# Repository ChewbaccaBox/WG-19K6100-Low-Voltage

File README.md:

# WG-19K6100-Low-Voltage
My version of the low voltage replacement board for the 6100 monitor.\
Larger / Through-hole parts provide beter thermals.\
Adjustable voltage range = +/- 23.5v - 28.5v \
&nbsp;

**BILL OF MATERIALS** :\
Includes example digikey item #'s

**1 * LM317 ( TO-220 pkg.)**\
&nbsp;&nbsp;&nbsp;&nbsp; DGK: LM317TG \
**1 * LM337 ( TO-220 pkg.)**\
&nbsp;&nbsp;&nbsp;&nbsp; DGK: LM3137TG \
**2 * 1k Trimmer Pot (PCB can fit both '.' and ... pin types, 0.1" spacing)**\
&nbsp;&nbsp;&nbsp;&nbsp; DGK: 500E-0331 or DGK:3306W-1-102\
**6 * 1N4007 Diode**\
**4 * 2.2uF 50V Capacitor**\
**2 * 10uF 50V Capacitor**\
**2 * 240 Ohm Resistor 1/4W**\
**4 * 4.5k Ohm Resistor 1/4W**\
**5 * WIRES TO RAISE PCB OVER BOARD**

**(OPTIONAL) 2 * TO-220 Compact Heatsink + Insulator/Thermal Pad** \
&nbsp;&nbsp;&nbsp;&nbsp; DGK: 577102B00000G + SP400-0.007-00-54 \
&nbsp;

**TESTING STATUS:**

Multiple installed and working in revisions P314 and P327.\
The filter capicators of the deflection board are closer to the connector on revision P327, so it is a little tighter, but will still work.

**INSTALLATION INSTRUCTIONS:**

To be written... Stay tuned!

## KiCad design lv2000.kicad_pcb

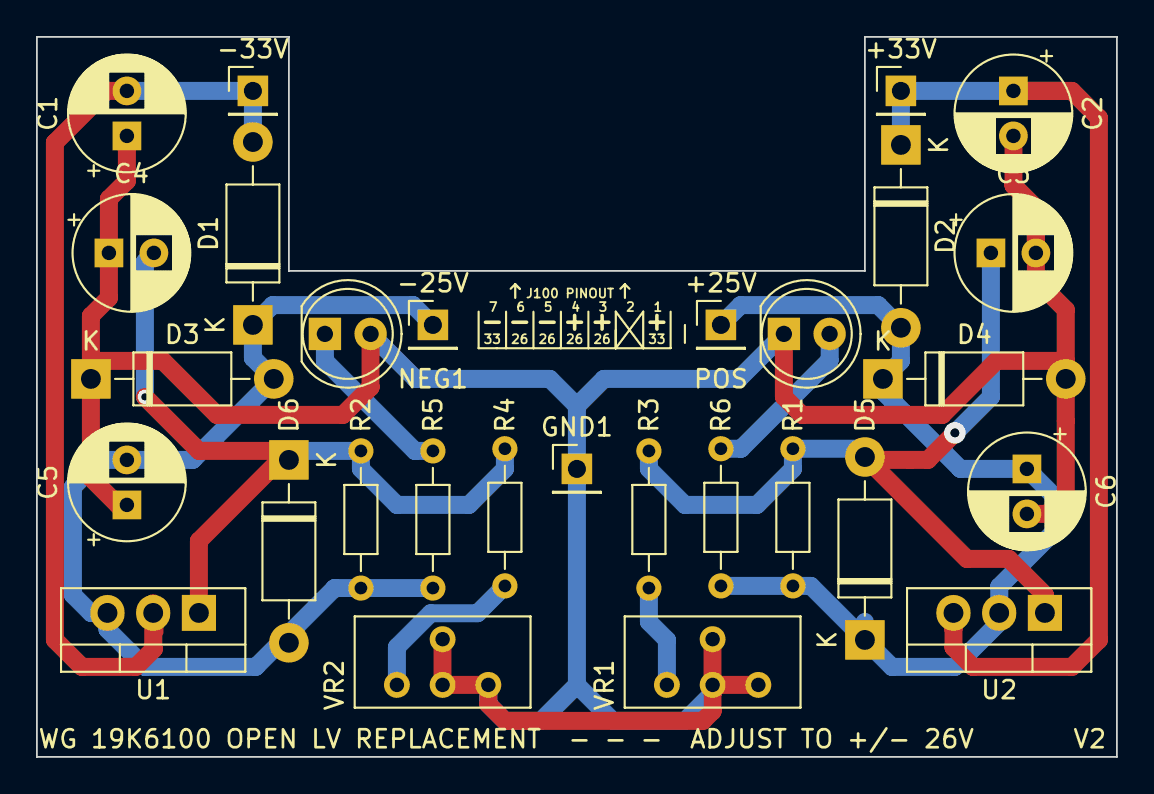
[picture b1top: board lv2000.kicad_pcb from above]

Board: 2 copper layers, 60.0 x 40.0 mm, 29 parts (0 on the bottom side), 11 nets.

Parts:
+25V, +33V: Conn_01x01_Male; PinHeader_1x01_P2.54mm_Vertical
-25V, -33V: Conn_01x01_Male; PinHeader_1x01_P2.54mm_Vertical
C1, C2, C3, C4, C5, C6: CP; CP_Radial_D6.3mm_P2.50mm
D1, D2, D3, D4, D5, D6: D; D_DO-41_SOD81_P10.16mm_Horizontal
GND1: Conn_01x01_Male; PinHeader_1x01_P2.54mm_Vertical
NEG1: LED; LED_D5.0mm_Clear
POS: LED; LED_D5.0mm_Clear
R1, R2, R3, R4, R5, R6: R; R_Axial_DIN0204_L3.6mm_D1.6mm_P7.62mm_Horizontal
U1: LM337_TO220; TO-220-3_Vertical
U2: LM317_TO-220; TO-220-3_Vertical
VR1, VR2: R_POT; Potentiometer_Bourns_3386C_Horizontal

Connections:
GND: C1.1, C2.2, C3.2, C4.1, C5.1, C6.2, D3.1, D4.2, GND1.1, NEG1.2, POS.1, VR1.2, VR1.3, VR2.2, VR2.3
unnamed: +25V.1, C6.1, D2.2, D4.1, D5.1, R1.1, R6.1, U2.2
unnamed: +33V.1, C2.1, D2.1, U2.3
unnamed: -25V.1, C5.2, D1.1, D3.2, D6.2, R2.2, R5.2, U1.3
unnamed: -33V.1, C1.2, D1.2, U1.2
unnamed: C3.1, D5.2, R1.2, R3.1, U2.1
unnamed: C4.2, D6.1, R2.1, R4.2, U1.1
unnamed: NEG1.1, R5.1
unnamed: POS.2, R6.2
unnamed: R3.2, VR1.1
unnamed: R4.1, VR2.1

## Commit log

2022-01-14 Update README.md
    updated testing status
2022-01-14 Update README.md
    changed text
2022-01-14 Update README.md
    updated text
2022-01-14 Update README.md
    update
2022-01-14 First commit
    need to organize and update
2022-01-14 Update README.md
    install to be done
2022-01-14 Create PCB
2022-01-14 Delete PCB
    didn't mean to
2022-01-14 Rename lv2000-cache.lib to PCB/lv2000-cache.lib
    Move to PCB folder
2022-01-14 Rename lv2000.kicad_pcb to PCB/lv2000.kicad_pcb
    Move to PCB folder
2022-01-14 Rename lv2000.kicad_pcb-bak to PCB/lv2000.kicad_pcb-bak
    Move to PCB folder
2022-01-14 Rename lv2000.pro to PCB/lv2000.pro
    Move to PCB folder
2022-01-14 Rename lv2000.sch to PCB/lv2000.sch
    Move to PCB folder
2022-01-14 Rename lv2000.sch-bak to PCB/lv2000.sch-bak
    Move to PCB folder
2022-01-14 Delete v1.zip
    wrong place
2022-01-14 Delete fp-info-cache
    wrong place
2022-06-01 Updating Repository
    updating stuff!
